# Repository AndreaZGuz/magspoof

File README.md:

# MagSpoof By Electronic Cats

# What is MagSpoof?

**MagSpoof by Electronic Cats** is a device that can spoof/emulate any magnetic stripe or credit card. It can work "wirelessly", even on **standard magstripe/credit card readers**, by generating a strong electromagnetic field that emulates a traditional magnetic stripe card.

* Allows you to store all of your credit cards and magstripes in one device
* Works on traditional magstripe readers **wirelessly** (no NFC/RFID required)
* Can **disable** Chip-and-PIN (code not included)
* Correctly **predicts** Amex credit card numbers + expirations from previous card number (code not included)
* Supports all three magnetic stripe tracks, and even supports Track 1+2 simultaneously
* Easy to build using Arduino or other common parts

MagSpoof can be used as a traditional credit card and simply store all of your credit cards (and with modification, can technically disable chip requirements) in various impressive and exciting form factors, or can be used for security research in any area that would traditionally require a magstripe, such as readers for credit cards, drivers licenses, hotel room keys, automated parking lot tickets, etc.

**Note**: The Chip-and-PIN and Amex information is **not** implemented and using MagSpoof requires you to have/own the magstripes that you wish to emulate. Simply having a credit card number and expiration is not enough to perform transactions. MagSpoof **does** allow you to perform research in other areas of magstripes, microcontrollers, and electromagnetism, as well as learn about and create your own devices similar to other existing, commercial technologies such as <a href="http://www.samsung.com/us/support/answer/ANS00043865/997410383/">Samsung MST</a> and <a href="https://onlycoin.com/">Coin</a>.</p>

### ⚠️ Disclaimer ⚠️
MagSpoof is a wireless penetration testing tool intended solely for use in authorized security audits, where such usage is permitted by applicable laws and regulations. Before utilizing this tool, it is crucial to ensure compliance with all relevant legal requirements and obtain appropriate permissions from the relevant authorities.

It is essential to note that the board does not provide any means or authorization to utilize credit cards or engage in any financial transactions that are not legally authorized. Electronic Cats holds no responsibility for any unauthorized use of the tool or any resulting damages.

-----

# Based in work of Samy Kamkar

**Point of Contact:** [@SamyKamkar](https://twitter.com/samykamkar)

You can see more of my projects at <http://samy.pl> or contact me at <code@samy.pl>.

------

# Wiki and Getting Started 

------
# License

Electronic Cats invests time and resources in providing this open-source design. Please support Electronic Cats and open-source hardware by purchasing products from Electronic Cats!

Designed by Electronic Cats.

Firmware released under an GNU AGPL v3.0 license. See the LICENSE file for more information.

Hardware released under an CERN Open Hardware Licence v1.2. See the LICENSE_HARDWARE file for more information.

Electronic Cats is a registered trademark, please do not use if you sell these PCBs.

30 Octuber 2019

------

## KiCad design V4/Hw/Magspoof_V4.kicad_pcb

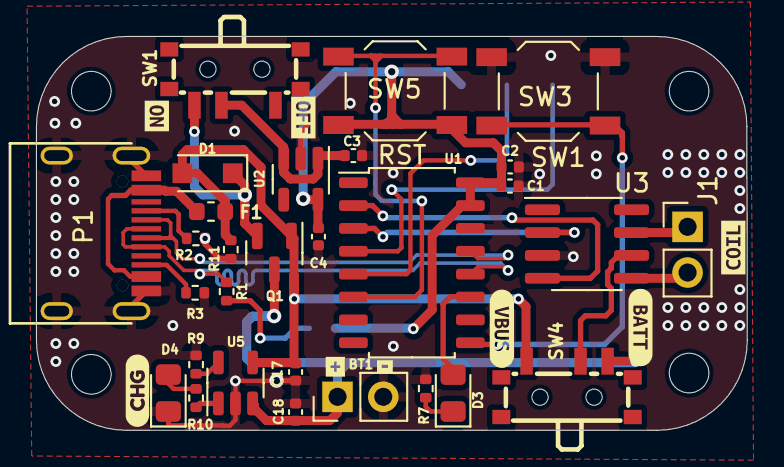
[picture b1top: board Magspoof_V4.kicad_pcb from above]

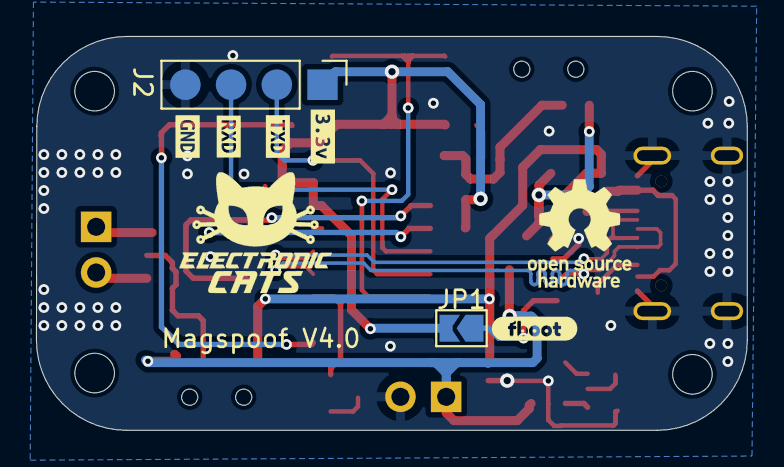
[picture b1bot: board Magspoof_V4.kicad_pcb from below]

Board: 2 copper layers, 39.5 x 21.9 mm, 48 parts (7 on the bottom side), 26 nets.

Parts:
BT1: Battery_Cell; PinHeader_1x02_P2.54mm_Vertical
C1, C2: 0.1uF; C_0402_1005Metric
C3, C4, C17, C18: 10uF; C_0402_1005Metric
D1: MBR120; D_SOD-123F
D3: Status; LED_0805_2012Metric_Pad1.15x1.40mm_HandSolder
D4: CHG; LED_0805_2012Metric_Pad1.15x1.40mm_HandSolder
F1: 0.5A; Fuse_0603_1608Metric
H1, H2, H3, H4: MountingHole; MountingHole_2.2mm_M2
J1: Coil; PinHeader_1x02_P2.54mm_Vertical
J2: SWD; PinHeader_1x04_P2.54mm_Vertical
JP1: boot; SolderJumper-2_P1.3mm_Open_TrianglePad1.0x1.5mm
P1: USB_C_Plug_USB2.0; C393939
Q1: DMG3415U-7; SOT-23
R1: 20K; R_0402_1005Metric
R2, R3, R9: 5.1k; R_0402_1005Metric
R7: 180R; R_0402_1005Metric
R10: 470; R_0402_1005Metric
R11: 100K; R_0402_1005Metric
SW1: ON; SW-SMD_SSSS811101
SW3: S1; SW_SPST_TL3342
SW4: SOURCE MAG; SW-SMD_SSSS811101
SW5: RESET; SW_SPST_TL3342
U1: CH552G; SOP-16_4.55x10.3mm_P1.27mm
U2: AP2112K-3.3; SOT-23-5
U3: TC4424; SOIC-8_3.9x4.9mm_P1.27mm
U5: MCP73831; SOT-23-5
kibuzzard-6435F1C7: G***; kibuzzard-6435F1C7
kibuzzard-6435F3C4: G***; kibuzzard-6435F3C4
kibuzzard-6435F22E: G***; kibuzzard-6435F22E
kibuzzard-6436E8D1: G***; kibuzzard-6436E8D1
kibuzzard-6436E8D8: G***; kibuzzard-6436E8D8
kibuzzard-6436EA37: G***; kibuzzard-6436EA37
kibuzzard-6436EA46: G***; kibuzzard-6436EA46
kibuzzard-6436EF9F: G***; kibuzzard-6436EF9F
kibuzzard-6436EF98: G***; kibuzzard-6436EF98
kibuzzard-64629FC5: G***; kibuzzard-64629FC5
kibuzzard-64629FDC: G***; kibuzzard-64629FDC
kibuzzard-64665C6A: G***; kibuzzard-64665C6A
kibuzzard-64665C9F: G***; kibuzzard-64665C9F

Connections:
+3V3: C1.1, C2.1, C4.1, J2.1, JP1.2 (B), SW5.2, U1.15 (VCC), U1.16 (V33), U2.5 (VOUT)
+BATT: BT1.1 (+), C18.1, Q1.3 (D), SW4.3 (C), U5.3 (VBAT)
/D+: P1.A6 (D+), R1.2, U1.12 (P3.6)
/D-: P1.A7 (D-), U1.13 (P3.7)
/IN_A: U1.2 (P1.4), U3.4 (IN_B)
/IN_B: U1.3 (P1.5), U3.2 (IN_A)
/LED: D3.2 (A), U1.11 (P3.4)
/Out_A: J1.1, U3.7 (OUT_A)
/Out_B: J1.2, U3.5 (OUT_B)
/RST: SW5.1, U1.6 (RST)
/RXD: J2.3, U1.4 (P1.6)
/SW1: SW3.2, U1.9 (P1.1)
/TXD: J2.2, U1.5 (P1.7)
GND: BT1.2 (-), C1.2, C2.2, C3.2, C4.2, C17.2, C18.2, D4.1 (K), J2.4, P1.A1 (GND), P1.S1 (SHIELD), R2.1, R3.1, R7.2, R9.2, R11.2, SW3.1, U1.14 (GND), U2.2 (GND), U3.3 (GND), U5.2 (VSS)
unnamed: D1.1 (K), Q1.2 (S), SW1.3 (A)
unnamed: D3.1 (K), R7.1
unnamed: D4.2 (A), R10.2
unnamed: F1.1, P1.A4 (VBUS)
unnamed: JP1.1 (A), R1.1
unnamed: P1.A5 (CC), R2.2
unnamed: P1.B5 (VCONN), R3.2
unnamed: C3.1, SW1.2 (B), U2.1 (VIN), U2.3 (EN)
unnamed: SW4.2 (B), U3.6 (VDD)
unnamed: R9.1, U5.5 (PROG)
unnamed: R10.1, U5.1 (STAT)
VBUS: C17.1, D1.2 (A), F1.2, Q1.1 (G), R11.1, SW4.1 (A), U5.4 (VDD)

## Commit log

2023-05-11 update gitignore
2023-05-11 upload firmware v4
2023-05-11 add lcsc components to BOM
2023-05-15 Change components for JLCPCB
2023-05-15 change footprint of SW1,4, and F1 and routing
2023-05-15 change SW1 and SW4 for stocks
2023-05-18 Update labels
2023-05-18 change DFN-8 to SOIC-8 TC4424 and add 3d model of SW1,4
2023-05-19 Update BOM
2023-06-02 firmware update
2023-06-02 update firmware v4
2023-06-05 fix serigraphy "SW1"for "RST"
2023-06-13 Update BOM (jlcpcb components)
2023-06-19 Add disclaimer
2023-06-29 add eeprom_magspoof (dev)
2023-06-30 test serial input tracks
2023-06-30 track1 read from EEPROM
2023-06-30 receive and play tracks by serial
2023-07-03 s (save) p(play) tracks serial commands
2023-07-04 fix index bug, ready for testing
2023-08-07 Change name to usbcdc_magpoof
2023-12-15 Update README.md
    Adding: wiki button
2023-12-19 Update README.md
    Product pictures; modifications: link to the store and link to the wiki
2023-12-19 Update README.md
    Pictures added
